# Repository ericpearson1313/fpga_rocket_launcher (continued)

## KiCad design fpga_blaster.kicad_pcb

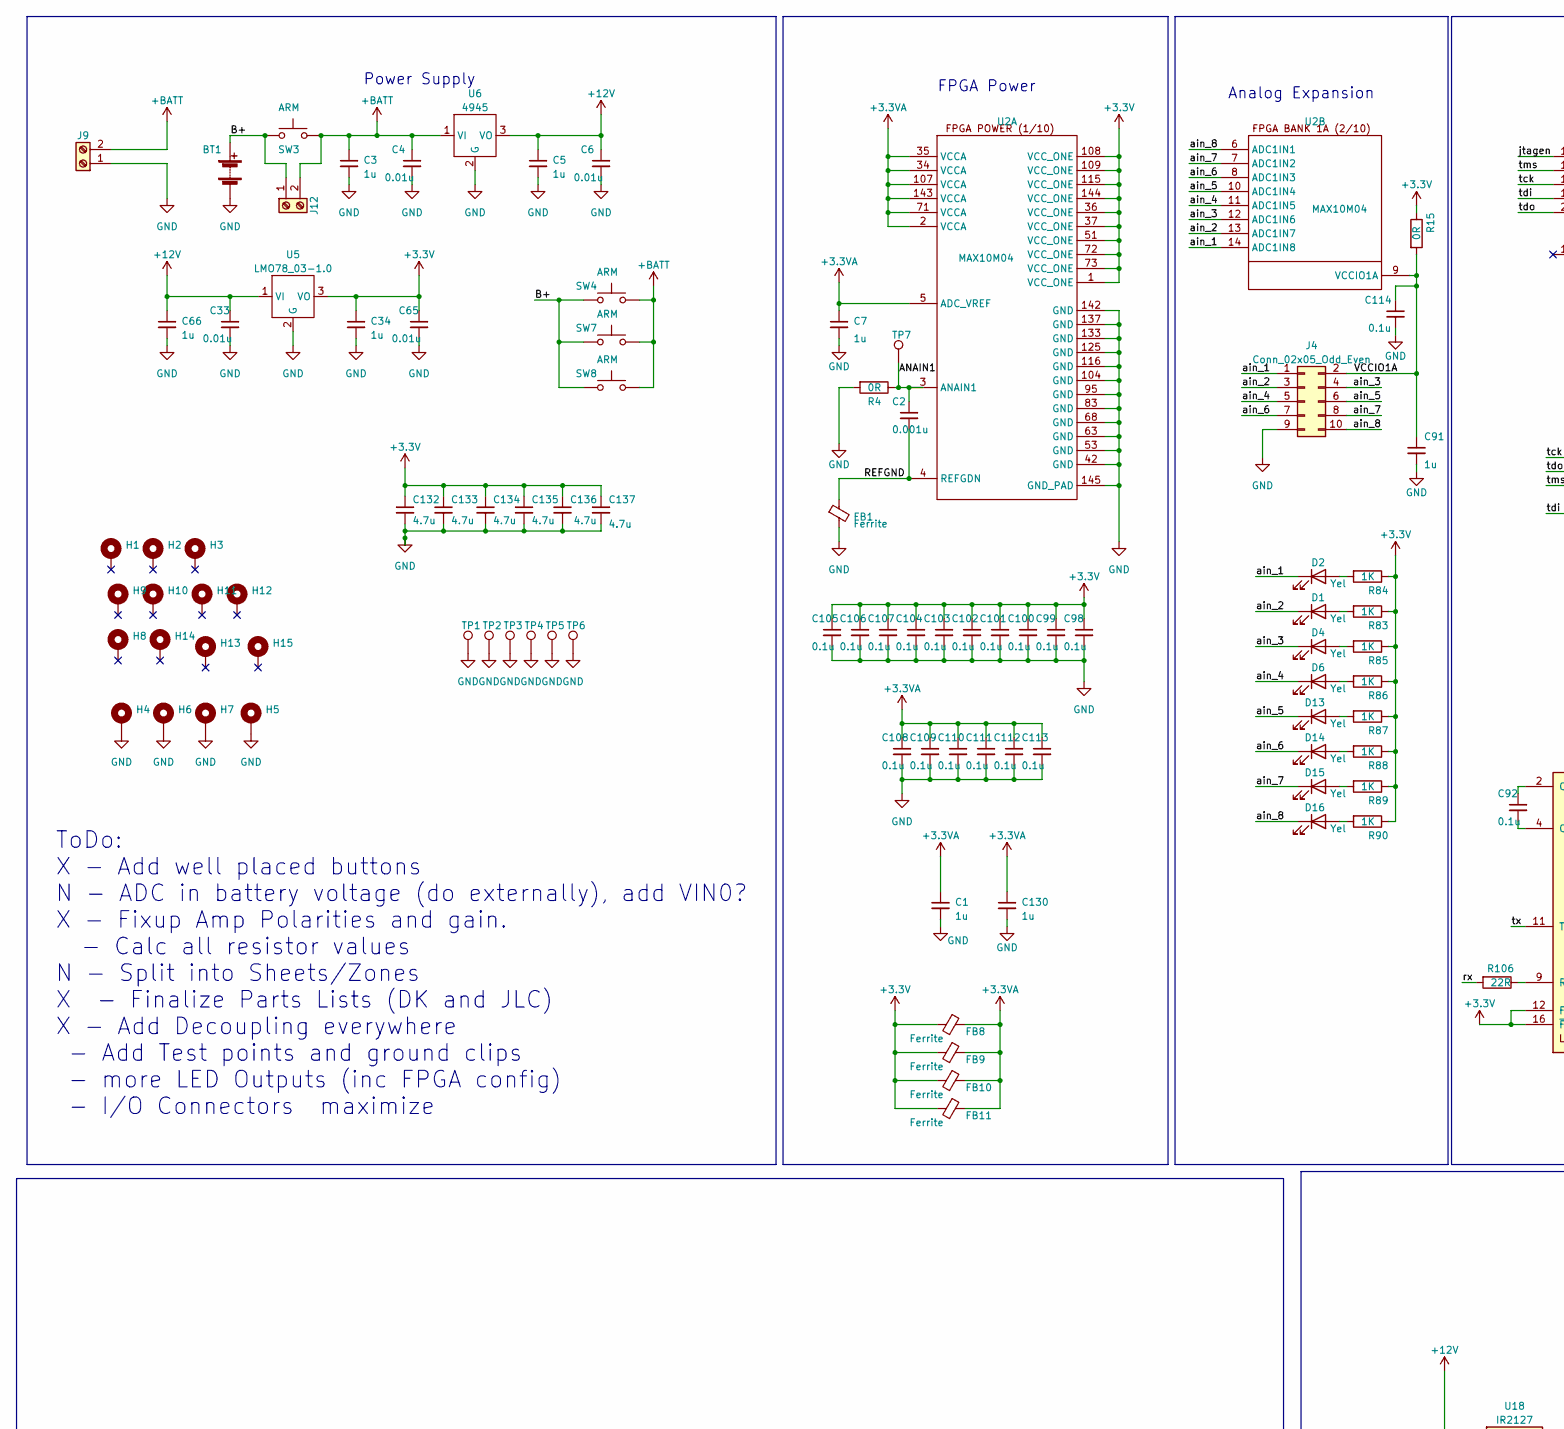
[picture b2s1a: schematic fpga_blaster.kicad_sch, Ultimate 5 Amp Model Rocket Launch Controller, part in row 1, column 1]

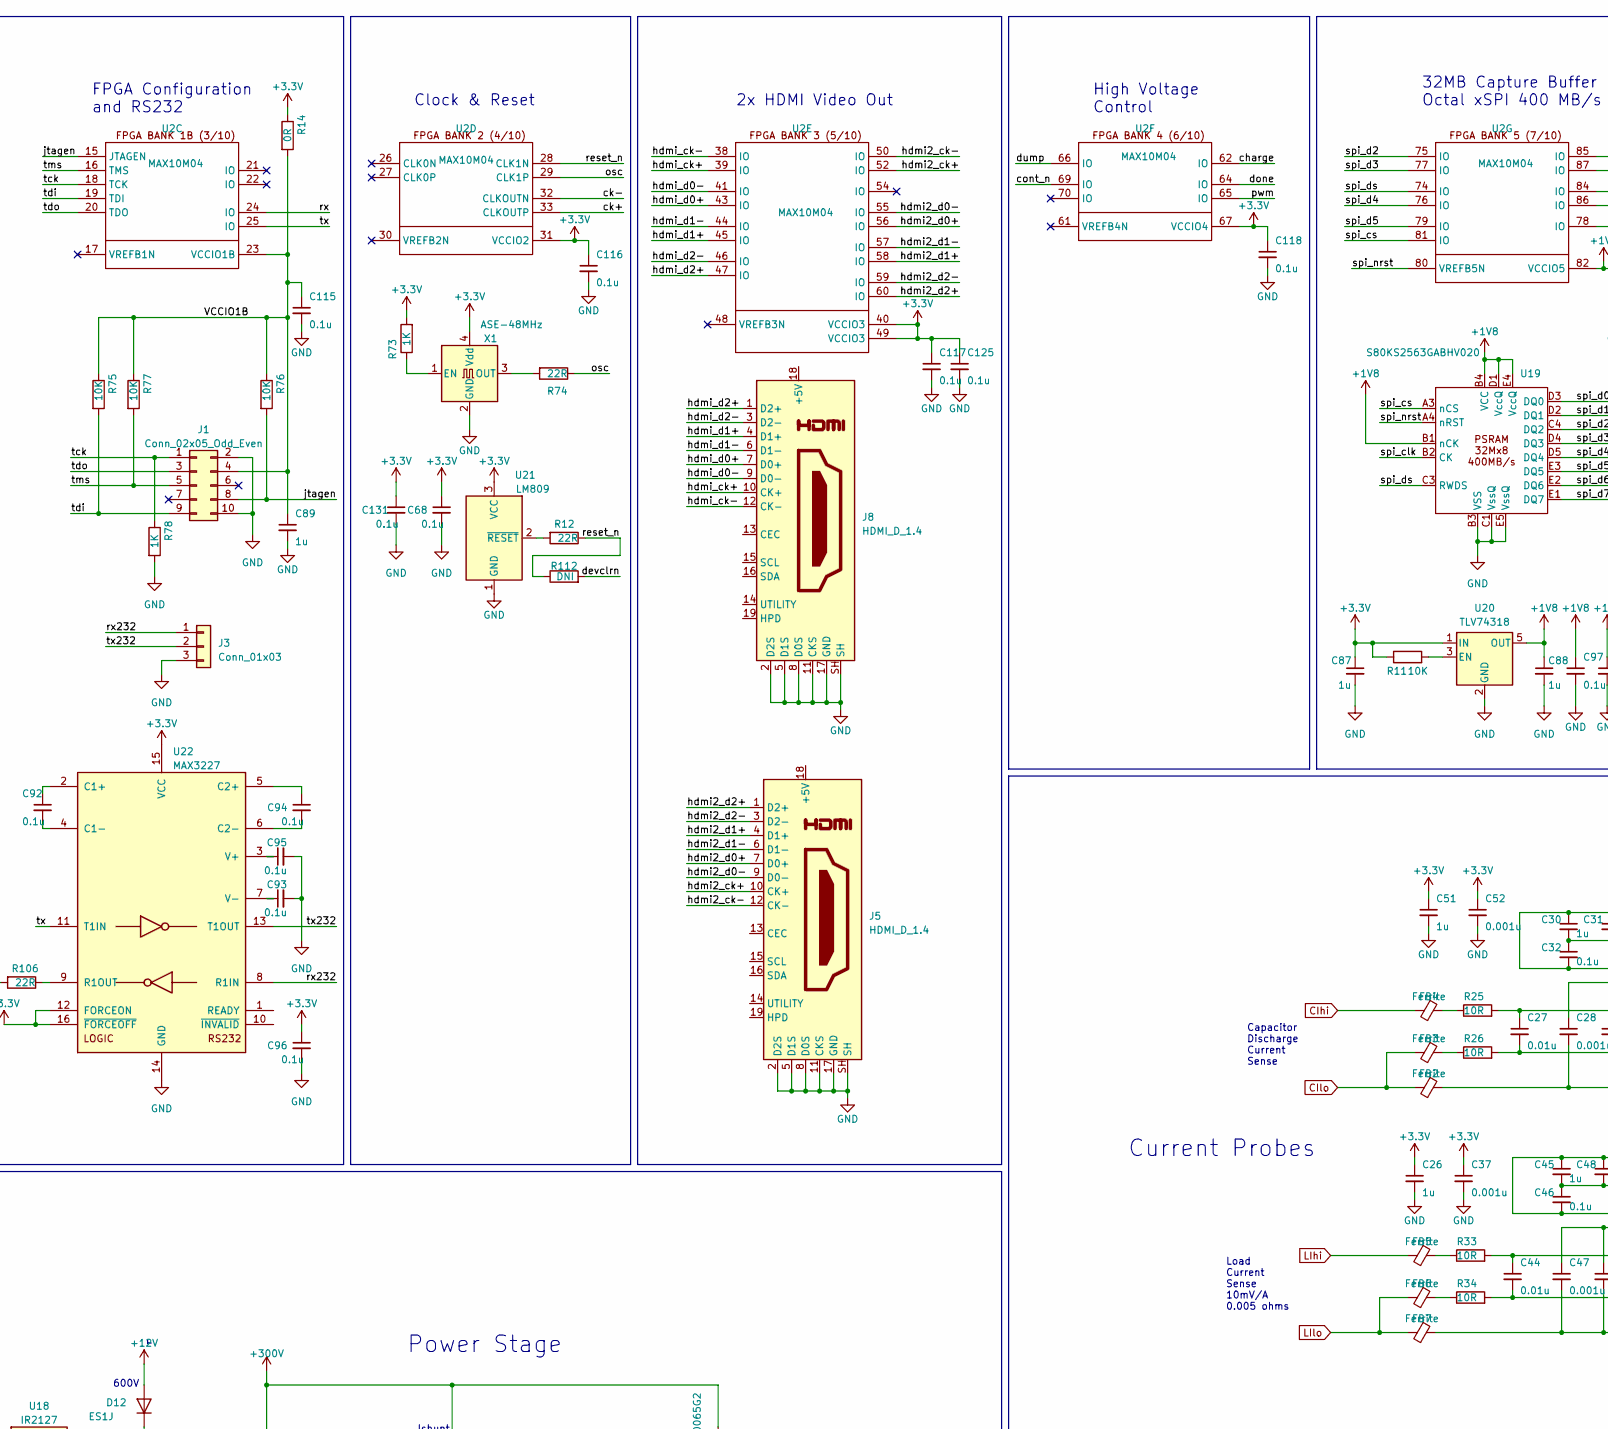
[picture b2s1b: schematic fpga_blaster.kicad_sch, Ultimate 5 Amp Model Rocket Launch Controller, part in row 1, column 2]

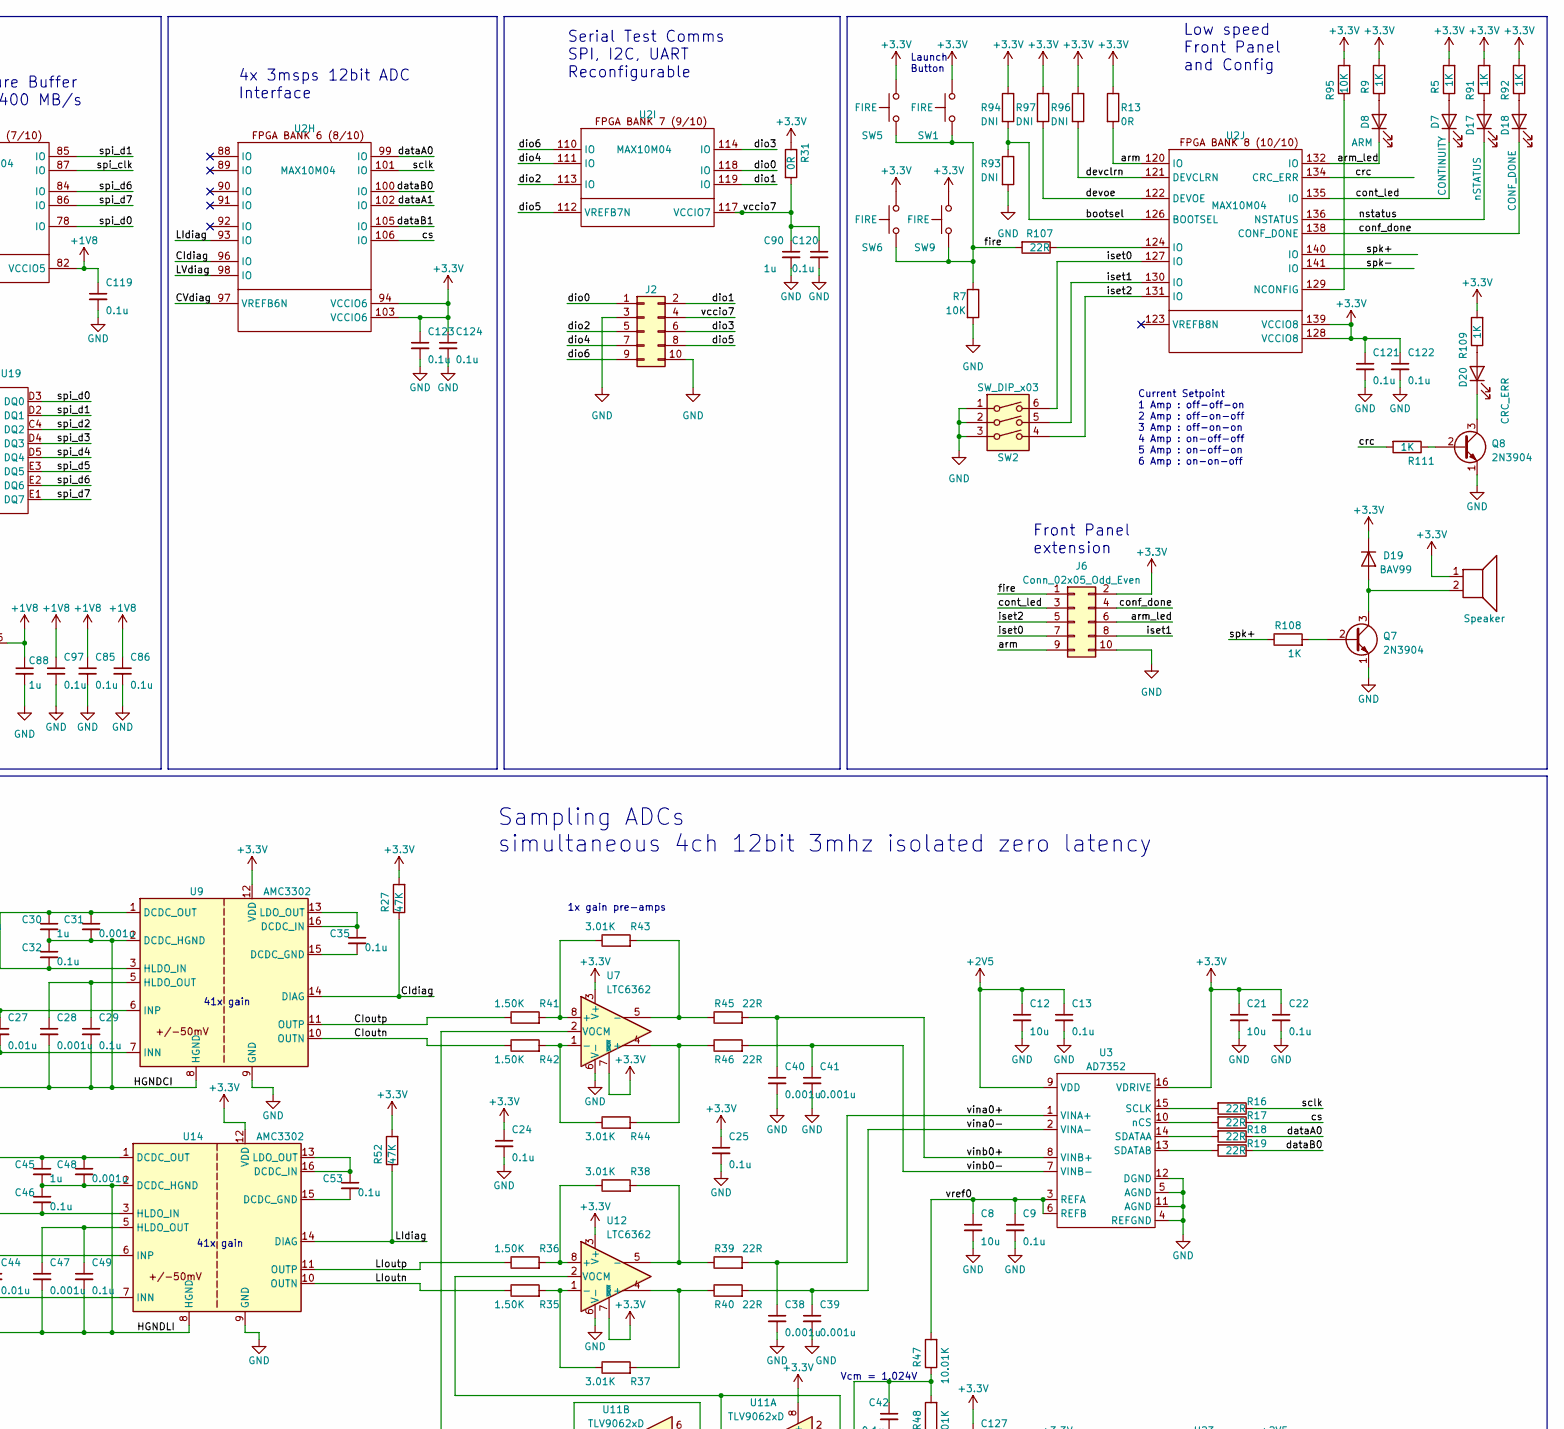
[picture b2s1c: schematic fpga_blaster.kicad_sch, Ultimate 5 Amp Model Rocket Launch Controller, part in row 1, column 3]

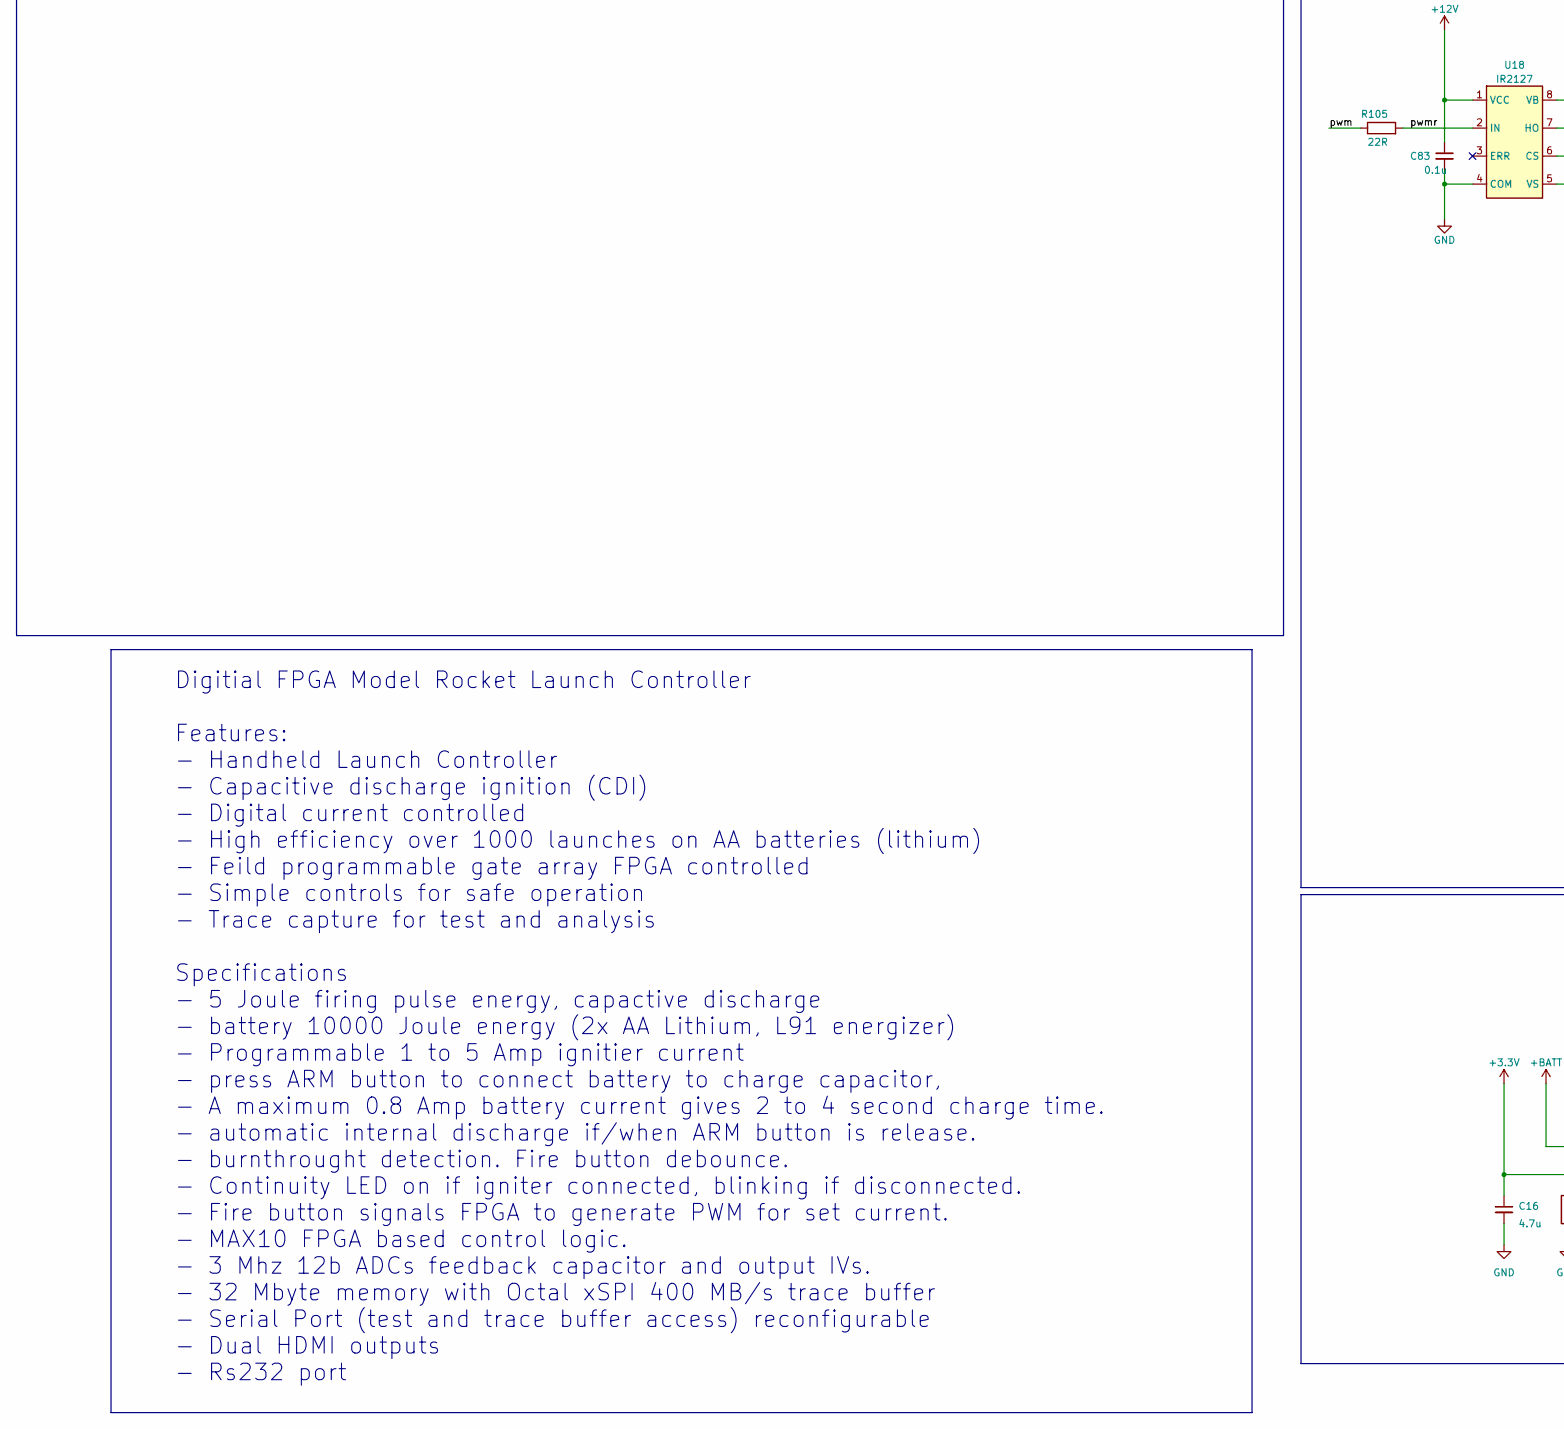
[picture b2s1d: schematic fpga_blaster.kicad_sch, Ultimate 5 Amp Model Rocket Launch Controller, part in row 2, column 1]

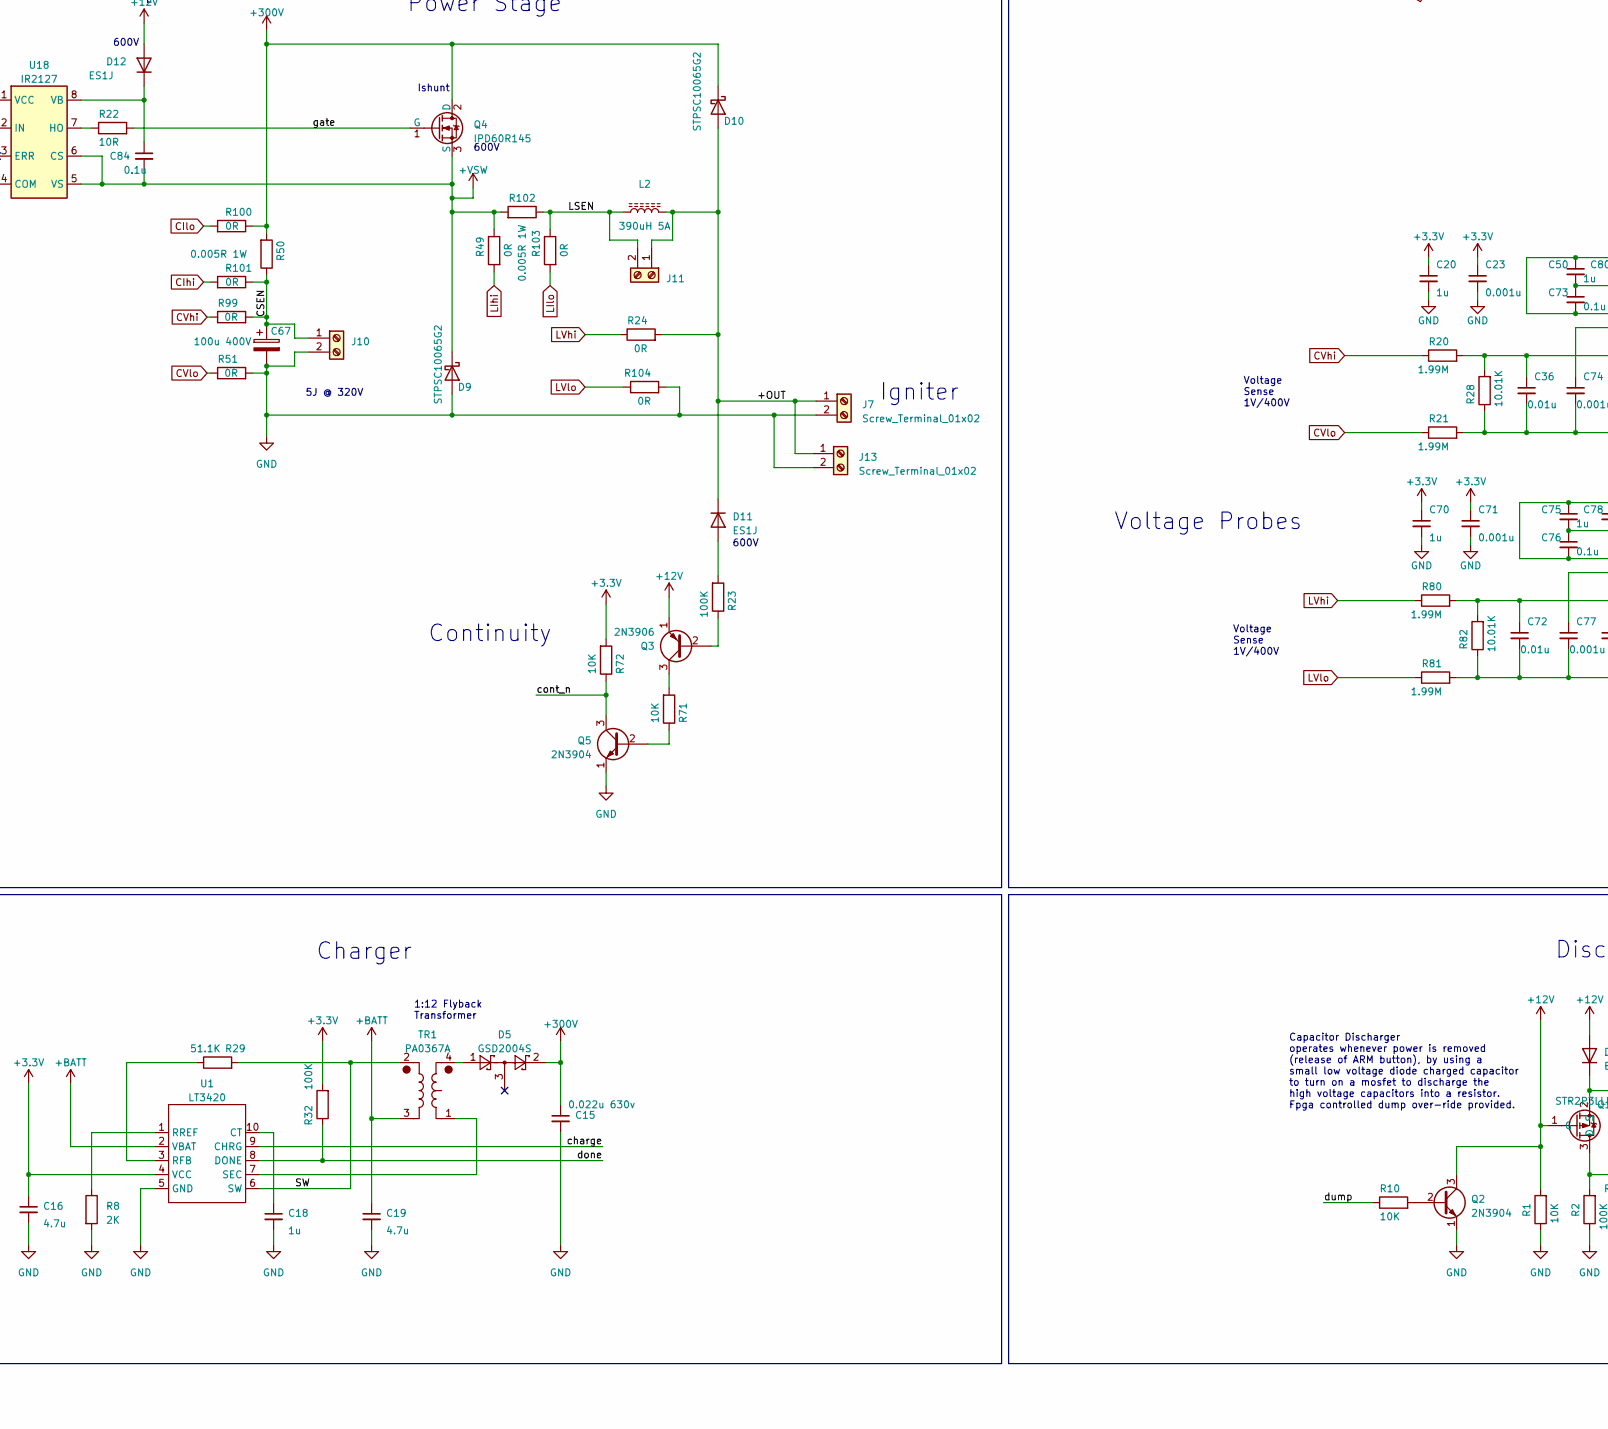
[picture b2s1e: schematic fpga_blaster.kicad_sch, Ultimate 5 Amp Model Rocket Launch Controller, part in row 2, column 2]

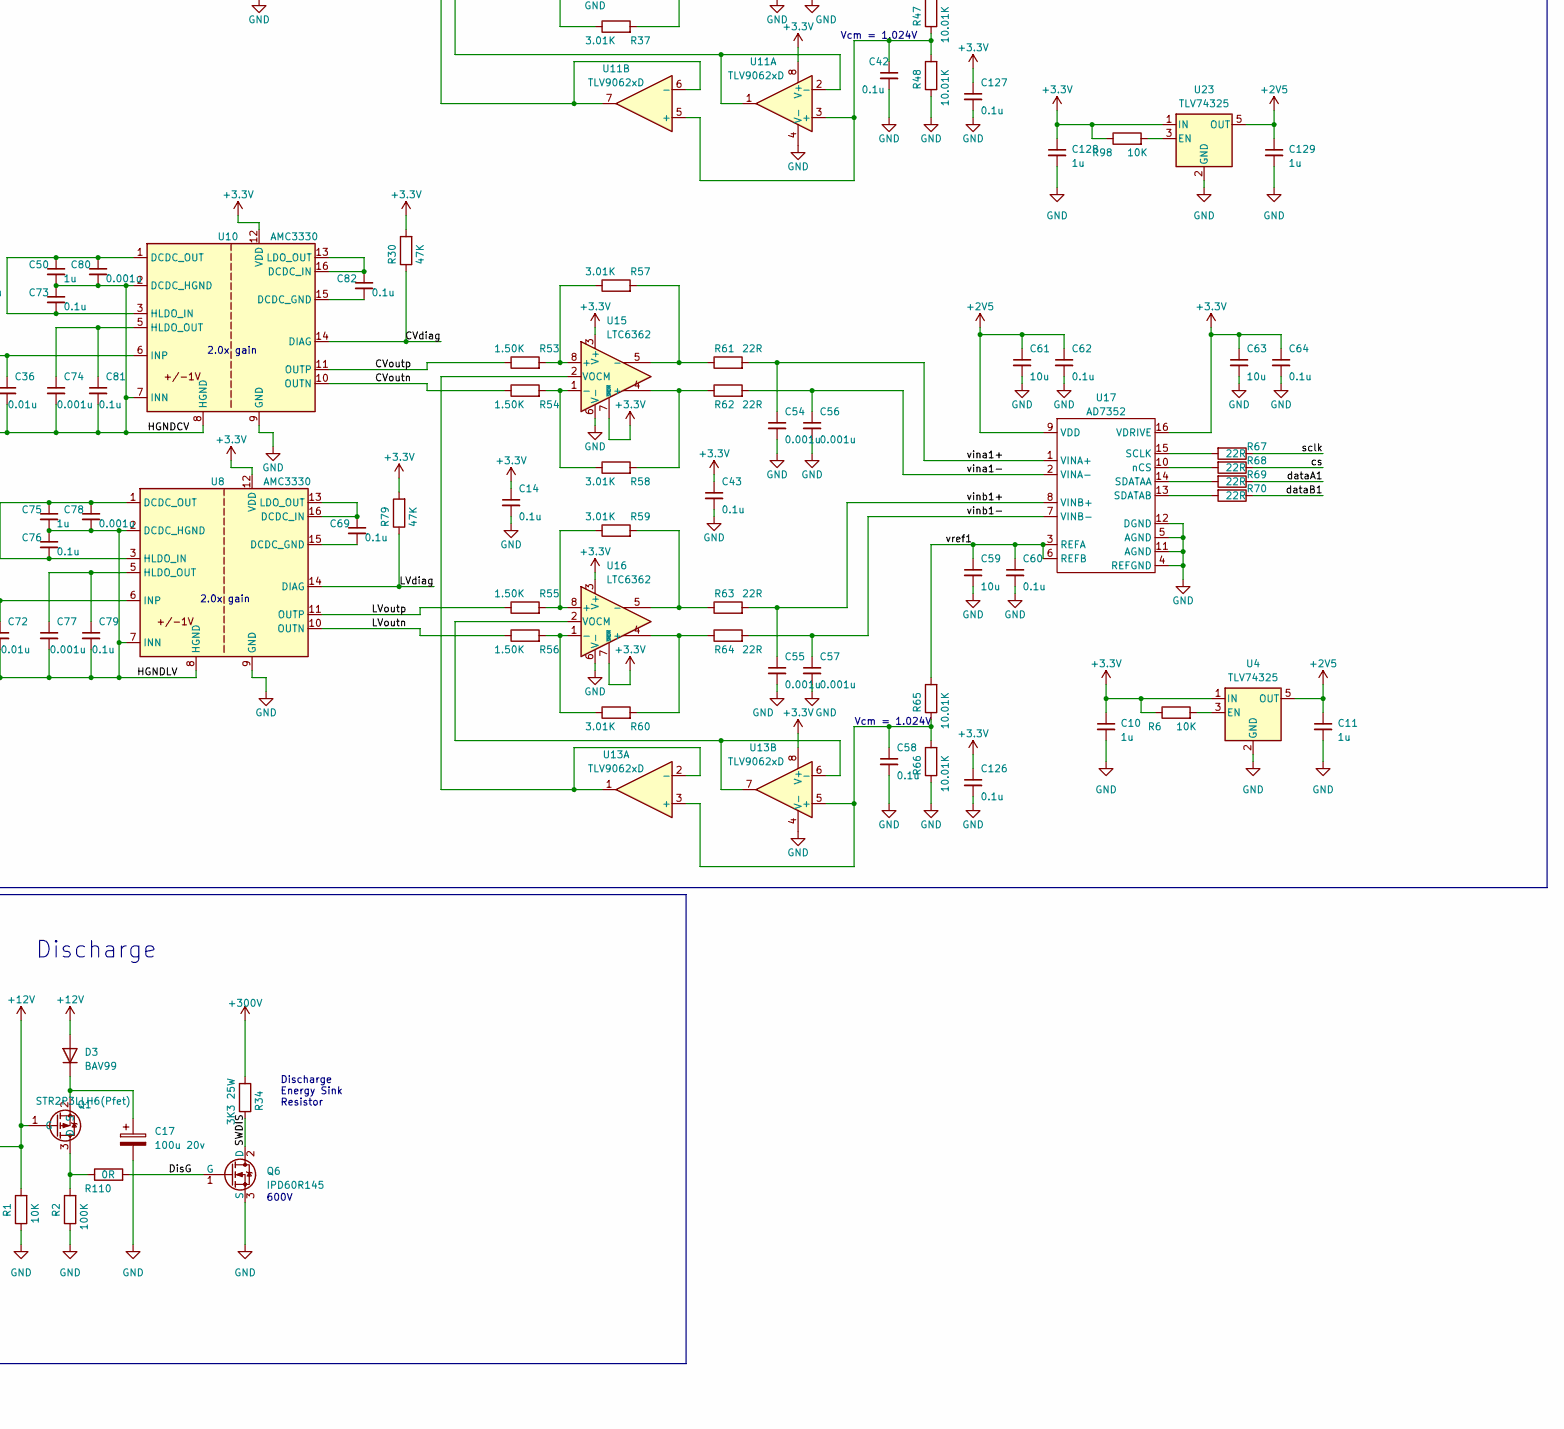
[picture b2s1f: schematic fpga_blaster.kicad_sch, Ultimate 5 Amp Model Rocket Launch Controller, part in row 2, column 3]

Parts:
BT1: BatteryHolder_Keystone_2462_2xAA
C1, C3, C5, C7, C10, C11, C18, C20, C26, C30, C34, C45, C50, C51, C66, C70, C75, C87, C88, C89, C90, C91, C128, C129, C130: 1u; C_0603_1608Metric
C2, C23, C28, C31, C37, C38, C39, C40, C41, C47, C48, C52, C54, C55, C56, C57, C71, C74, C77, C78, C80: 0.001u; C_0603_1608Metric
C4, C6, C27, C33, C36, C44, C65, C72: 0.01u; C_0603_1608Metric
C8, C12, C21, C59, C61, C63: 10u; C_1206_3216Metric
C9, C13, C14, C22, C24, C25, C29, C32, C35, C42, C43, C46, C49, C53, C58, C60, C62, C64, C68, C69, C73, C76, C79, C81, C82, C83, C84, C85, C86, C92, C93, C94, C95, C96, C97, C98, C99, C100, C101, C102, C103, C104, C105, C106, C107, C108, C109, C110, C111, C112, C113, C114, C115, C116, C117, C118, C119, C120, C121, C122, C123, C124, C125, C126, C127, C131: 0.1u; C_0603_1608Metric
C15: 0.022u 630v; C_1206_3216Metric
C16, C19, C132, C133, C134, C135, C136, C137: 4.7u; C_1206_3216Metric
C17: 100u 20v; C_Radial_D5.0mm_H7.0mm_P2.00mm
C67: 100u 400V; CP_Radial_D16.0mm_P7.50mm
D1, D2, D4, D6, D13, D14, D15, D16: Yel; LED_0603_1608Metric
D3, D19: BAV99; SOT-23; JLC C7420336
D5: GSD2004S; SOT-23; JLC C85606
D7: CONTINUITY; LED_0603_1608Metric
D8: ARM; LED_0603_1608Metric
D9, D10: ‎STPSC10065G2; TO-263-2_TabPin1; JLC C602663
D11, D12: ES1J; D_SMA; JLC C99410
D17: nSTATUS; LED_0603_1608Metric
D18: CONF_DONE; LED_0603_1608Metric
D20: CRC_ERR; LED_0603_1608Metric
FB1, FB2, FB3, FB4, FB5, FB6, FB7, FB8, FB9, FB10, FB11: Ferrite; L_0603_1608Metric
H1, H2, H3, H4, H5, H6, H7, H8, H9, H10, H11, H12, H13, H14, H15: MountingHole_3mm_Pad
J1, J2, J4, J6: Conn_02x05_Odd_Even; PinHeader_2x05_P2.54mm_Vertical
J3: Conn_01x03; PinHeader_1x03_P2.54mm_Vertical
J5, J8: HDMI_D_1.4; HDMI_A_Amphenol_10029449-x01xLF_Horizontal
J7, J9, J10, J11, J12, J13: Screw_Terminal_01x02; TerminalBlock_Phoenix_MKDS-1,5-2-5.08_1x02_P5.08mm_Horizont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
L2: 390uH 5A; L_Toroid_Vertical_L35.6mm_W17.8mm_P12.70mm_Pulse_E
LS1: Speaker; PUIAudio_SMT_0825_S_4_R
Q1: STR2P3LLH6(Pfet); SOT-23
Q2, Q5, Q7, Q8: 2N3904; SOT-23
Q3: 2N3906; SOT-23; JLC C909755
Q4, Q6: IPD60R145; TO-252-2; JLC C3277918
R1, R7: 10K; R_0603_1608Metric; JLC C491211
R2, R32: 100K; R_0603_1608Metric; JLC C319967
R4, R13: 0R; R_0603_1608Metric; JLC C491211
R5, R9, R73, R78, R83, R84, R85, R86, R87, R88, R89, R90, R91, R92, R108, R109, R111: 1K; R_0603_1608Metric; JLC C319967
R6, R11, R98: 10K; R_0603_1608Metric; JLC C778416
R8: 2K; R_0603_1608Metric; JLC C319700
R10, R71, R72: 10K; R_0603_1608Metric
R12, R16, R17, R18, R19, R67, R68, R69, R70, R74, R106, R107: 22R; R_0603_1608Metric; JLC C319967
R14, R15, R31, R110: 0R; R_0603_1608Metric; JLC C319967
R20, R21, R80, R81: 1.99M; R_0603_1608Metric; JLC C778416
R22, R25, R26, R33, R34: 10R; R_0603_1608Metric; JLC C778416
R23: 100K; R_0603_1608Metric; JLC C491211
R24, R49, R51, R99, R100, R101, R103, R104: 0R; R_0603_1608Metric; JLC C778416
R27, R30, R52, R79: 47K; R_0603_1608Metric; JLC C778416
R28, R47, R48, R65, R66, R82: 10.01K; R_0603_1608Metric; JLC C778416
R29: 51.1K; R_0603_1608Metric; JLC C234563
R35, R36, R41, R42, R53, R54, R55, R56: 1.50K; R_0603_1608Metric; JLC C778416
R37, R38, R43, R44, R57, R58, R59, R60: 3.01K; R_0603_1608Metric; JLC C778416
R39, R40, R45, R46, R61, R62, R63, R64, R105: 22R; R_0603_1608Metric; JLC C778416
R50, R102: 0.005R 1W; R_2818 current sense
R75, R76, R77, R95: 10K; R_0603_1608Metric; JLC C319967
R93, R94, R96, R97, R112: DNI; R_0603_1608Metric; JLC C491211
SW1, SW5, SW6, SW9: FIRE; SW_SPST_HP03
SW2: SW_DIP_x03; SW_DIP_SPSTx03_Slide_Omron_A6S-310x_W8.9mm_P2.54mm
SW3, SW4, SW7, SW8: ARM; SW_SPST_HP03
TP1, TP2, TP3, TP4, TP5, TP6, TP7: TestPoint_Keystone_5000-5004_Miniature
TR1: PA0367A; PA0637A Pulse Coil; JLC C5382098
U1: LT3420; MSOP-10_3x3mm_P0.5mm; JLC C670531
U2: MAX10M04; EQFP-144-1EP_20x20mm_P0.5mm_EP8.93x8.7mm_ThermalVias
U3, U17: AD7352; TSSOP-16_4.4x5mm_P0.65mm
U4, U23: TLV74325; SOT-23-5
U5: LMO78_03-1.0; TO-220-3_Vertical
U6: 4945; TO-220-3_Vertical
U7, U12, U15, U16: LTC6362; MSOP-8_3x3mm_P0.65mm
U8, U10: AMC3330; SOIC-16W_7.5x10.3mm_P1.27mm
U9, U14: AMC3302; SOIC-16W_7.5x10.3mm_P1.27mm
U11, U13: TLV9062xD; SOT-23-8
U18: IR2127; SOIC-8_3.9x4.9mm_P1.27mm; JLC C356723
U19: S80KS2563GABHV020; FBGA-24_6mmx8mm_Layout5x5_P1.00mm
U20: TLV74318; SOT-23-5
U21: LM809; SOT-23
U22: MAX3227; SSOP-16_5.3x6.2mm_P0.65mm
X1: ASE-48MHz; Oscillator_SMD_Abracon_ASV-4Pin_7.0x5.1mm_HandSoldering

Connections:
+1V8: C85.1, C86.1, C88.1, C97.1, C119.1, U2.82 (VCCIO5), U19.B1 (nCK), U19.B4 (VCC), U19.D1 (VccQ), U19.E4 (VccQ), U20.5 (OUT)
+2V5: C11.1, C12.1, C13.1, C61.1, C62.1, C129.1, U3.9 (VDD), U4.5 (OUT), U17.9 (VDD), U23.5 (OUT)
+3.3V: C10.1, C14.1, C16.1, C20.1, C21.1, C22.1, C23.1, C24.1, C25.1, C26.1, C34.1, C37.1, C43.1, C51.1, C52.1, C63.1, C64.1, C65.1, C68.1, C70.1, C71.1, C87.1, C96.1, C98.1, C99.1, C100.1, C101.1, C102.1, C103.1, C104.1, C105.1, C106.1, C107.1, C116.1, C117.1, C118.1, C121.1, C122.1, C123.1, C124.1, C125.1, C126.1, C127.1, C128.1, C131.1, C132.1, C133.1, C134.1, C135.1, C136.1, C137.1, D19.1 (K), FB8.1, FB9.1, FB10.1, FB11.1, J6.2, LS1.1, R5.2, R6.1, R9.2, R11.1, R13.1, R14.1, R15.1, R27.2, R30.2, R31.1, R32.2, R52.2, R72.2, R73.2, R79.2, R83.1, R84.1, R85.1, R86.1, R87.1, R88.1, R89.1, R90.1, R91.2, R92.2, R94.1, R95.2, R96.1, R97.1, R98.1, R109.2, SW1.2, SW5.2, SW6.2, SW9.2, U1.4 (VCC), U2.1 (VCC_ONE), U2.31 (VCCIO2), U2.36 (VCC_ONE), U2.37 (VCC_ONE), U2.40 (VCCIO3), U2.49 (VCCIO3), U2.51 (VCC_ONE), U2.67 (VCCIO4), U2.72 (VCC_ONE), U2.73 (VCC_ONE), U2.94 (VCCIO6), U2.103 (VCCIO6), U2.108 (VCC_ONE), U2.109 (VCC_ONE), U2.115 (VCC_ONE), U2.128 (VCCIO8), U2.139 (VCCIO8), U2.144 (VCC_ONE), U3.16 (VDRIVE), U4.1 (IN), U5.3 (VO), U7.3 (V+), U7.7 (~SHDN), U8.12 (VDD), U9.12 (VDD), U10.12 (VDD), U11.8 (V+), U12.3 (V+), U12.7 (~SHDN), U13.8 (V+), U14.12 (VDD), U15.3 (V+), U15.7 (~SHDN), U16.3 (V+), U16.7 (~SHDN), U17.16 (VDRIVE), U20.1 (IN), U21.3 (VCC), U22.12 (FORCEON), U22.15 (VCC), U22.16 (~FORCEOFF), U23.1 (IN), X1.4 (Vdd)
+3.3VA: C1.1, C7.1, C108.1, C109.1, C110.1, C111.1, C112.1, C113.1, C130.1, FB8.2, FB9.2, FB10.2, FB11.2, U2.2 (VCCA), U2.5 (ADC_VREF), U2.34 (VCCA), U2.35 (VCCA), U2.71 (VCCA), U2.107 (VCCA), U2.143 (VCCA)
+12V: C5.1, C6.1, C33.1, C66.1, C83.1, D3.2 (A), D12.2 (A), Q1.1 (G), Q2.3 (C), Q3.1 (E), R1.2, U5.1 (VI), U6.3 (VO), U18.1 (VCC)
+BATT: C3.1, C4.1, C19.1, J9.2, J12.2, SW3.2, SW4.2, SW7.2, SW8.2, TR1.3, U1.2 (VBAT), U6.1 (VI)
+VSW: C84.2, D9.2 (K), Q4.3 (S), R49.1, R102.2, U18.5 (VS), U18.6 (CS)
/+OUT: D10.1 (A), D11.1 (K), J7.1, J11.1, J13.1, L2.2, R24.2
/ANAIN1: C2.1, R4.1, TP7.1, U2.3 (ANAIN1)
/B+: BT1.1 (+), J12.1, SW3.1, SW4.1, SW7.1, SW8.1
/CIdiag: R27.1, U2.96 (IO), U9.14 (DIAG)
/CIoutn: R42.1, U9.10 (OUTN)
/CIoutp: R41.1, U9.11 (OUTP)
/CSEN: C67.1, J10.1, R50.1, R99.2, R101.1
/CVdiag: R30.1, U2.97 (VREFB6N), U10.14 (DIAG)
/CVoutn: R54.1, U10.10 (OUTN)
/CVoutp: R53.1, U10.11 (OUTP)
/DisG: Q6.1 (G), R110.2
/HGNDCI: C28.2, C29.2, C30.2, C31.2, C32.1, FB2.1, U9.2 (DCDC_HGND), U9.8 (HGND)
/HGNDCV: C36.2, C50.2, C73.1, C74.2, C80.2, C81.2, R21.2, R28.1, U10.2 (DCDC_HGND), U10.7 (INN), U10.8 (HGND)
/HGNDLI: C45.2, C46.1, C47.2, C48.2, C49.2, FB7.1, U14.2 (DCDC_HGND), U14.8 (HGND)
/HGNDLV: C72.2, C75.2, C76.1, C77.2, C78.2, C79.2, R81.2, R82.1, U8.2 (DCDC_HGND), U8.7 (INN), U8.8 (HGND)
/LIdiag: R52.1, U2.93 (IO), U14.14 (DIAG)
/LIoutn: R35.1, U14.10 (OUTN)
/LIoutp: R36.1, U14.11 (OUTP)
/LSEN: J11.2, L2.1, R102.1, R103.1
/LVdiag: R79.1, U2.98 (IO), U8.14 (DIAG)
/LVoutn: R56.1, U8.10 (OUTN)
/LVoutp: R55.1, U8.11 (OUTP)
/REFGND: C2.2, FB1.1, U2.4 (REFGDN)
/SW: R29.2, TR1.2, U1.6 (SW)
/VCCIO1A: C91.1, C114.1, J4.2, R15.2, U2.9 (VCCIO1A)
/VCCIO1B: C89.1, C115.1, J1.4, R14.2, R75.1, R76.1, R77.1, U2.23 (VCCIO1B)
/ain_1: D2.1 (K), J4.1, U2.14 (ADC1IN8)
/ain_2: D1.1 (K), J4.3, U2.13 (ADC1IN7)
/ain_3: D4.1 (K), J4.4, U2.12 (ADC1IN6)
/ain_4: D6.1 (K), J4.5, U2.11 (ADC1IN5)
/ain_5: D13.1 (K), J4.6, U2.10 (ADC1IN4)
/ain_6: D14.1 (K), J4.7, U2.8 (ADC1IN3)
/ain_7: D15.1 (K), J4.8, U2.7 (ADC1IN2)
/ain_8: D16.1 (K), J4.10, U2.6 (ADC1IN1)
/arm: J6.9, R13.2, U2.120 (IO)
/arm_led: D8.1 (K), J6.6, U2.132 (IO)
/bootsel: R93.1, R94.2, U2.126 (BOOTSEL)
/charge: U1.9 (CHRG), U2.62 (IO)
/ck+: U2.33 (CLKOUTP)
/ck-: U2.32 (CLKOUTN)
/conf_done: D18.1 (K), J6.4, U2.138 (CONF_DONE)
/cont_led: D7.1 (K), J6.3, U2.135 (IO)
/cont_n: Q5.3 (C), R72.1, U2.69 (IO)
/crc: R111.2, U2.134 (CRC_ERR)
/cs: R17.1, R68.1, U2.106 (IO)
/dataA0: R18.1, U2.99 (IO)
/dataA1: R69.1, U2.102 (IO)
/dataB0: R19.1, U2.100 (IO)
/dataB1: R70.1, U2.105 (IO)
/devclrn: R96.2, R112.2, U2.121 (DEVCLRN)
/devoe: R97.2, U2.122 (DEVOE)
/dio0: J2.1, U2.118 (IO)
/dio1: J2.2, U2.119 (IO)
/dio2: J2.5, U2.113 (IO)
/dio3: J2.6, U2.114 (IO)
/dio4: J2.7, U2.111 (IO)
/dio5: J2.8, U2.112 (VREFB7N)
/dio6: J2.9, U2.110 (IO)
/done: R32.1, U1.8 (DONE), U2.64 (IO)
/dump: R10.1, U2.66 (IO)
/fire: J6.1, R7.1, R107.2, SW1.1, SW5.1, SW6.1, SW9.1
/gate: Q4.1 (G), R22.2
/hdmi2_ck+: J5.10 (CK+), U2.52 (IO)
/hdmi2_ck-: J5.12 (CK-), U2.50 (IO)
/hdmi2_d0+: J5.7 (D0+), U2.56 (IO)
/hdmi2_d0-: J5.9 (D0-), U2.55 (IO)
/hdmi2_d1+: J5.4 (D1+), U2.58 (IO)
/hdmi2_d1-: J5.6 (D1-), U2.57 (IO)
/hdmi2_d2+: J5.1 (D2+), U2.60 (IO)
/hdmi2_d2-: J5.3 (D2-), U2.59 (IO)
/hdmi_ck+: J8.10 (CK+), U2.39 (IO)
/hdmi_ck-: J8.12 (CK-), U2.38 (IO)
/hdmi_d0+: J8.7 (D0+), U2.43 (IO)
/hdmi_d0-: J8.9 (D0-), U2.41 (IO)
/hdmi_d1+: J8.4 (D1+), U2.45 (IO)
/hdmi_d1-: J8.6 (D1-), U2.44 (IO)
/hdmi_d2+: J8.1 (D2+), U2.47 (IO)
/hdmi_d2-: J8.3 (D2-), U2.46 (IO)
/iset0: J6.7, SW2.6, U2.127 (IO)
/iset1: J6.8, SW2.5, U2.130 (IO)
/iset2: J6.5, SW2.4, U2.131 (IO)
/jtagen: J1.8, R76.2, U2.15 (JTAGEN)
/nstatus: D17.1 (K), U2.136 (NSTATUS)
/osc: R74.1, U2.29 (CLK1P)
/pwm: R105.1, U2.65 (IO)
/pwmr: R105.2, U18.2 (IN)
/reset_n: R12.1, R112.1, U2.28 (CLK1N)
/rx: R106.2, U2.24 (IO)
/rx232: J3.1, U22.8 (R1IN)
/sclk: R16.1, R67.1, U2.101 (IO)
/spi_clk: U2.87 (IO), U19.B2 (CK)
/spi_cs: U2.81 (IO), U19.A3 (nCS)
/spi_d0: U2.78 (IO), U19.D3 (DQ0)
/spi_d1: U2.85 (IO), U19.D2 (DQ1)
/spi_d2: U2.75 (IO), U19.C4 (DQ2)
/spi_d3: U2.77 (IO), U19.D4 (DQ3)
/spi_d4: U2.76 (IO), U19.D5 (DQ4)
/spi_d5: U2.79 (IO), U19.E3 (DQ5)
/spi_d6: U2.84 (IO), U19.E2 (DQ6)
/spi_d7: U2.86 (IO), U19.E1 (DQ7)
/spi_ds: U2.74 (IO), U19.C3 (RWDS)
/spi_nrst: U2.80 (VREFB5N), U19.A4 (nRST)
/spk+: R108.1, U2.140 (IO)
/spk-: U2.141 (IO)
/tck: J1.1, R78.1, U2.18 (TCK)
/tdi: J1.9, R75.2, U2.19 (TDI)
/tdo: J1.3, U2.20 (TDO)
/tms: J1.5, R77.2, U2.16 (TMS)
/tx: U2.25 (IO), U22.11 (T1IN)
/tx232: J3.2, U22.13 (T1OUT)
/vccio7: C90.1, C120.1, J2.4, R31.2, U2.117 (VCCIO7)
/vina0+: C38.1, R39.2, U3.1 (VINA+)
/vina0-: C39.1, R40.2, U3.2 (VINA-)
/vina1+: C54.1, R61.2, U17.1 (VINA+)
/vina1-: C56.1, R62.2, U17.2 (VINA-)
/vinb0+: C40.1, R45.2, U3.8 (VINB+)
/vinb0-: C41.1, R46.2, U3.7 (VINB-)
/vinb1+: C55.1, R63.2, U17.8 (VINB+)
/vinb1-: C57.1, R64.2, U17.7 (VINB-)
/vref0: C8.1, C9.1, R47.2, U3.3 (REFA), U3.6 (REFB)
/vref1: C59.1, C60.1, R65.2, U17.3 (REFA), U17.6 (REFB)
CIhi: FB4.2, R101.2
CIlo: FB2.2, FB3.2, R100.2
CVhi: R20.1, R99.1
CVlo: R21.1, R51.1
GND: BT1.2 (-), C1.2, C3.2, C4.2, C5.2, C6.2, C7.2, C8.2, C9.2, C10.2, C11.2, C12.2, C13.2, C14.2, C15.2, C16.2, C17.2, C18.2, C19.2, C20.2, C21.2, C22.2, C23.2, C24.2, C25.2, C26.2, C33.2, C34.2, C37.2, C38.2, C39.2, C40.2, C41.2, C42.2, C43.2, C51.2, C52.2, C54.2, C55.2, C56.2, C57.2, C58.2, C59.2, C60.2, C61.2, C62.2, C63.2, C64.2, C65.2, C66.2, C67.2, C68.2, C70.2, C71.2, C83.2, C85.2, C86.2, C87.2, C88.2, C89.2, C90.2, C91.2, C93.2, C95.2, C96.2, C97.2, C98.2, C99.2, C100.2, C101.2, C102.2, C103.2, C104.2, C105.2, C106.2, C107.2, C108.2, C109.2, C110.2, C111.2, C112.2, C113.2, C114.2, C115.2, C116.2, C117.2, C118.2, C119.2, C120.2, C121.2, C122.2, C123.2, C124.2, C125.2, C126.2, C127.2, C128.2, C129.2, C130.2, C131.2, C132.2, C133.2, C134.2, C135.2, C136.2, C137.2, D9.1 (A), FB1.2, H4.1, H5.1, H6.1, H7.1, J1.2, J1.10, J2.3, J2.10, J3.3, J4.9, J5.2 (D2S), J5.5 (D1S), J5.8 (D0S), J5.11 (CKS), J5.17 (GND), J5.SH, J6.10, J7.2, J8.2 (D2S), J8.5 (D1S), J8.8 (D0S), J8.11 (CKS), J8.17 (GND), J8.SH, J9.1, J10.2, J13.2, Q2.1 (E), Q5.1 (E), Q6.3 (S), Q7.1 (E), Q8.1 (E), R1.1, R2.1, R4.2, R7.2, R8.2, R48.1, R51.2, R66.1, R78.2, R93.2, R104.2, SW2.1, SW2.2, SW2.3, TP1.1, TP2.1, TP3.1, TP4.1, TP5.1, TP6.1, U1.5 (GND), U2.42 (GND), U2.53 (GND), U2.63 (GND), U2.68 (GND), U2.83 (GND), U2.95 (GND), U2.104 (GND), U2.116 (GND), U2.125 (GND), U2.133 (GND), U2.137 (GND), U2.142 (GND), U2.145 (GND_PAD), U3.4 (REFGND), U3.5 (AGND), U3.11 (AGND), U3.12 (DGND), U4.2 (GND), U5.2 (G), U6.2 (G), U7.6 (V-), U8.9 (GND), U9.9 (GND)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
LIhi: FB5.2, R49.2
LIlo: FB6.2, FB7.2, R103.2
LVhi: R24.1, R80.1
LVlo: R81.1, R104.1
unnamed: D1.2 (A), R83.2
unnamed: D2.2 (A), R84.2
unnamed: C17.1, D3.1 (K), Q1.2 (S)
unnamed: D4.2 (A), R85.2
unnamed: D5.1, TR1.4
unnamed: D6.2 (A), R86.2
unnamed: D7.2 (A), R5.1
unnamed: D8.2 (A), R9.1
unnamed: D11.2 (A), R23.2
unnamed: C84.1, D12.1 (K), U18.8 (VB)
unnamed: D13.2 (A), R87.2
unnamed: D14.2 (A), R88.2
unnamed: D15.2 (A), R89.2
unnamed: D16.2 (A), R90.2
unnamed: D17.2 (A), R91.1
unnamed: D18.2 (A), R92.1
unnamed: D19.2 (A), LS1.2, Q7.3 (C)
unnamed: D20.2 (A), R109.1
unnamed: D20.1 (K), Q8.3 (C)
unnamed: FB3.1, R26.1
unnamed: FB4.1, R25.1
unnamed: FB5.1, R33.1
unnamed: Q1.3 (D), R2.2, R110.1
unnamed: Q2.2 (B), R10.2
unnamed: Q3.2 (B), R23.1
unnamed: Q3.3 (C), R71.2
unnamed: Q5.2 (B), R71.1
unnamed: Q7.2 (B), R108.2
unnamed: Q8.2 (B), R111.1
unnamed: R35.2, R37.1, U12.1 (-)
unnamed: R36.2, R38.1, U12.8 (+)
unnamed: R37.2, R40.1, U12.4 (+)
unnamed: R38.2, R39.1, U12.5 (-)
unnamed: R41.2, R43.1, U7.8 (+)
unnamed: R42.2, R44.1, U7.1 (-)
unnamed: R43.2, R45.1, U7.5 (-)
unnamed: R44.2, R46.1, U7.4 (+)
unnamed: R53.2, R57.1, U15.8 (+)
unnamed: R54.2, R58.1, U15.1 (-)
unnamed: R55.2, R59.1, U16.8 (+)
unnamed: R56.2, R60.1, U16.1 (-)
unnamed: R57.2, R61.1, U15.5 (-)
unnamed: R58.2, R62.1, U15.4 (+)
unnamed: R59.2, R63.1, U16.5 (-)
unnamed: R60.2, R64.1, U16.4 (+)
unnamed: R107.1, U2.124 (IO)
unnamed: C18.1, U1.10 (CT)
unnamed: R29.1, U1.3 (RFB)
unnamed: R8.1, U1.1 (RREF)
unnamed: TR1.1, U1.7 (SEC)
unnamed: R95.1, U2.129 (NCONFIG)
unnamed: R16.2, U3.15 (SCLK)
unnamed: R18.2, U3.14 (SDATAA)
unnamed: R19.2, U3.13 (SDATAB)
unnamed: R17.2, U3.10 (nCS)
unnamed: R6.2, U4.3 (EN)
unnamed: C69.2, U8.15 (DCDC_GND)
unnamed: C69.1, U8.13 (LDO_OUT), U8.16 (DCDC_IN)
unnamed: C75.1, C76.2, C78.1, U8.1 (DCDC_OUT), U8.3 (HLDO_IN)
unnamed: C77.1, C79.1, U8.5 (HLDO_OUT)
unnamed: C72.1, R80.2, R82.2, U8.6 (INP)
unnamed: C35.2, U9.15 (DCDC_GND)
unnamed: C35.1, U9.13 (LDO_OUT), U9.16 (DCDC_IN)
unnamed: C30.1, C31.1, C32.2, U9.1 (DCDC_OUT), U9.3 (HLDO_IN)
unnamed: C28.1, C29.1, U9.5 (HLDO_OUT)
unnamed: C27.2, R26.2, U9.7 (INN)
unnamed: C27.1, R25.2, U9.6 (INP)
unnamed: C82.2, U10.15 (DCDC_GND)
unnamed: C82.1, U10.13 (LDO_OUT), U10.16 (DCDC_IN)
unnamed: C50.1, C73.2, C80.1, U10.1 (DCDC_OUT), U10.3 (HLDO_IN)
unnamed: C74.1, C81.1, U10.5 (HLDO_OUT)
unnamed: C36.1, R20.2, R28.2, U10.6 (INP)
unnamed: C42.1, R47.1, R48.2, U11.3 (+), U11.5 (+)
unnamed: U11.1, U11.2 (-), U12.2 (VOCM)
unnamed: U7.2 (VOCM), U11.6 (-), U11.7
unnamed: C58.1, R65.1, R66.2, U13.3 (+), U13.5 (+)
unnamed: U13.1, U13.2 (-), U15.2 (VOCM)
unnamed: U13.6 (-), U13.7, U16.2 (VOCM)
unnamed: C53.2, U14.15 (DCDC_GND)
unnamed: C53.1, U14.13 (LDO_OUT), U14.16 (DCDC_IN)
unnamed: C45.1, C46.2, C48.1, U14.1 (DCDC_OUT), U14.3 (HLDO_IN)
unnamed: C47.1, C49.1, U14.5 (HLDO_OUT)
unnamed: C44.1, R33.2, U14.6 (INP)
unnamed: R67.2, U17.15 (SCLK)
unnamed: R69.2, U17.14 (SDATAA)
unnamed: R70.2, U17.13 (SDATAB)
unnamed: R68.2, U17.10 (nCS)
unnamed: R22.1, U18.7 (HO)
unnamed: R11.2, U20.3 (EN)
unnamed: R12.2, U21.2 (~RESET)
unnamed: C92.1, U22.2 (C1+)
unnamed: C92.2, U22.4 (C1-)
unnamed: C94.1, U22.5 (C2+)
unnamed: C94.2, U22.6 (C2-)
unnamed: R106.1, U22.9 (R1OUT)
unnamed: C95.1, U22.3 (V+)
unnamed: C93.1, U22.7 (V-)
unnamed: R98.2, U23.3 (EN)
unnamed: R73.1, X1.1 (EN)
unnamed: R74.2, X1.3 (OUT)

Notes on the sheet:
600V
Front Panel extension
Discharge
Igniter
4x 3msps 12bit ADC Interface
32MB Capture Buffer Octal xSPI 400 MB/s
41x gain
2x HDMI Video Out
Voltage Sense 1V/400V
Voltage Probes
Ishunt
Sampling ADCs simultaneous 4ch 12bit 3mhz isolated zero latency
FPGA Power
2.0x gain
FPGA Configuration and RS232
Vcm = 1.024V
Continuity
Discharge Energy Sink Resistor
Capacitor Discharge Current Sense
Digitial FPGA Model Rocket Launch Controller Features: - Handheld Launch Controller - Capacitive discharge ignition (CDI) - Digital current controlled - High efficiency over 1000 launches on AA batteries (lithium) - Feild programmable gate array FPGA controlled - Simple controls for safe operation 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
Serial Test Comms SPI, I2C, UART Reconfigurable
5J @ 320V
Power Supply
Low speed Front Panel and Config
Power Stage
Analog Expansion
Current Probes
1x gain pre-amps
Current Setpoint 1 Amp : off-off-on 2 Amp : off-on-off 3 Amp : off-on-on 4 Amp : on-off-off 5 Amp : on-off-on 6 Amp : on-on-off
Load Current Sense 10mV/A 0.005 ohms
Capacitor Discharger operates whenever power is removed (release of ARM button), by using a small low voltage diode charged capacitor to turn on a mosfet to discharge the high voltage capacitors into a resistor. Fpga controlled dump over-ride provided.
1:12 Flyback Transformer
High Voltage Control
Launch Button
Charger
Clock & Reset
ToDo: X - Add well placed buttons N - ADC in battery voltage (do externally), add VIN0? X - Fixup Amp Polarities and gain. - Calc all resistor values N - Split into Sheets/Zones X - Finalize Parts Lists (DK and JLC) X - Add Decoupling everywhere - Add Test points and ground clips - more LED Outputs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
